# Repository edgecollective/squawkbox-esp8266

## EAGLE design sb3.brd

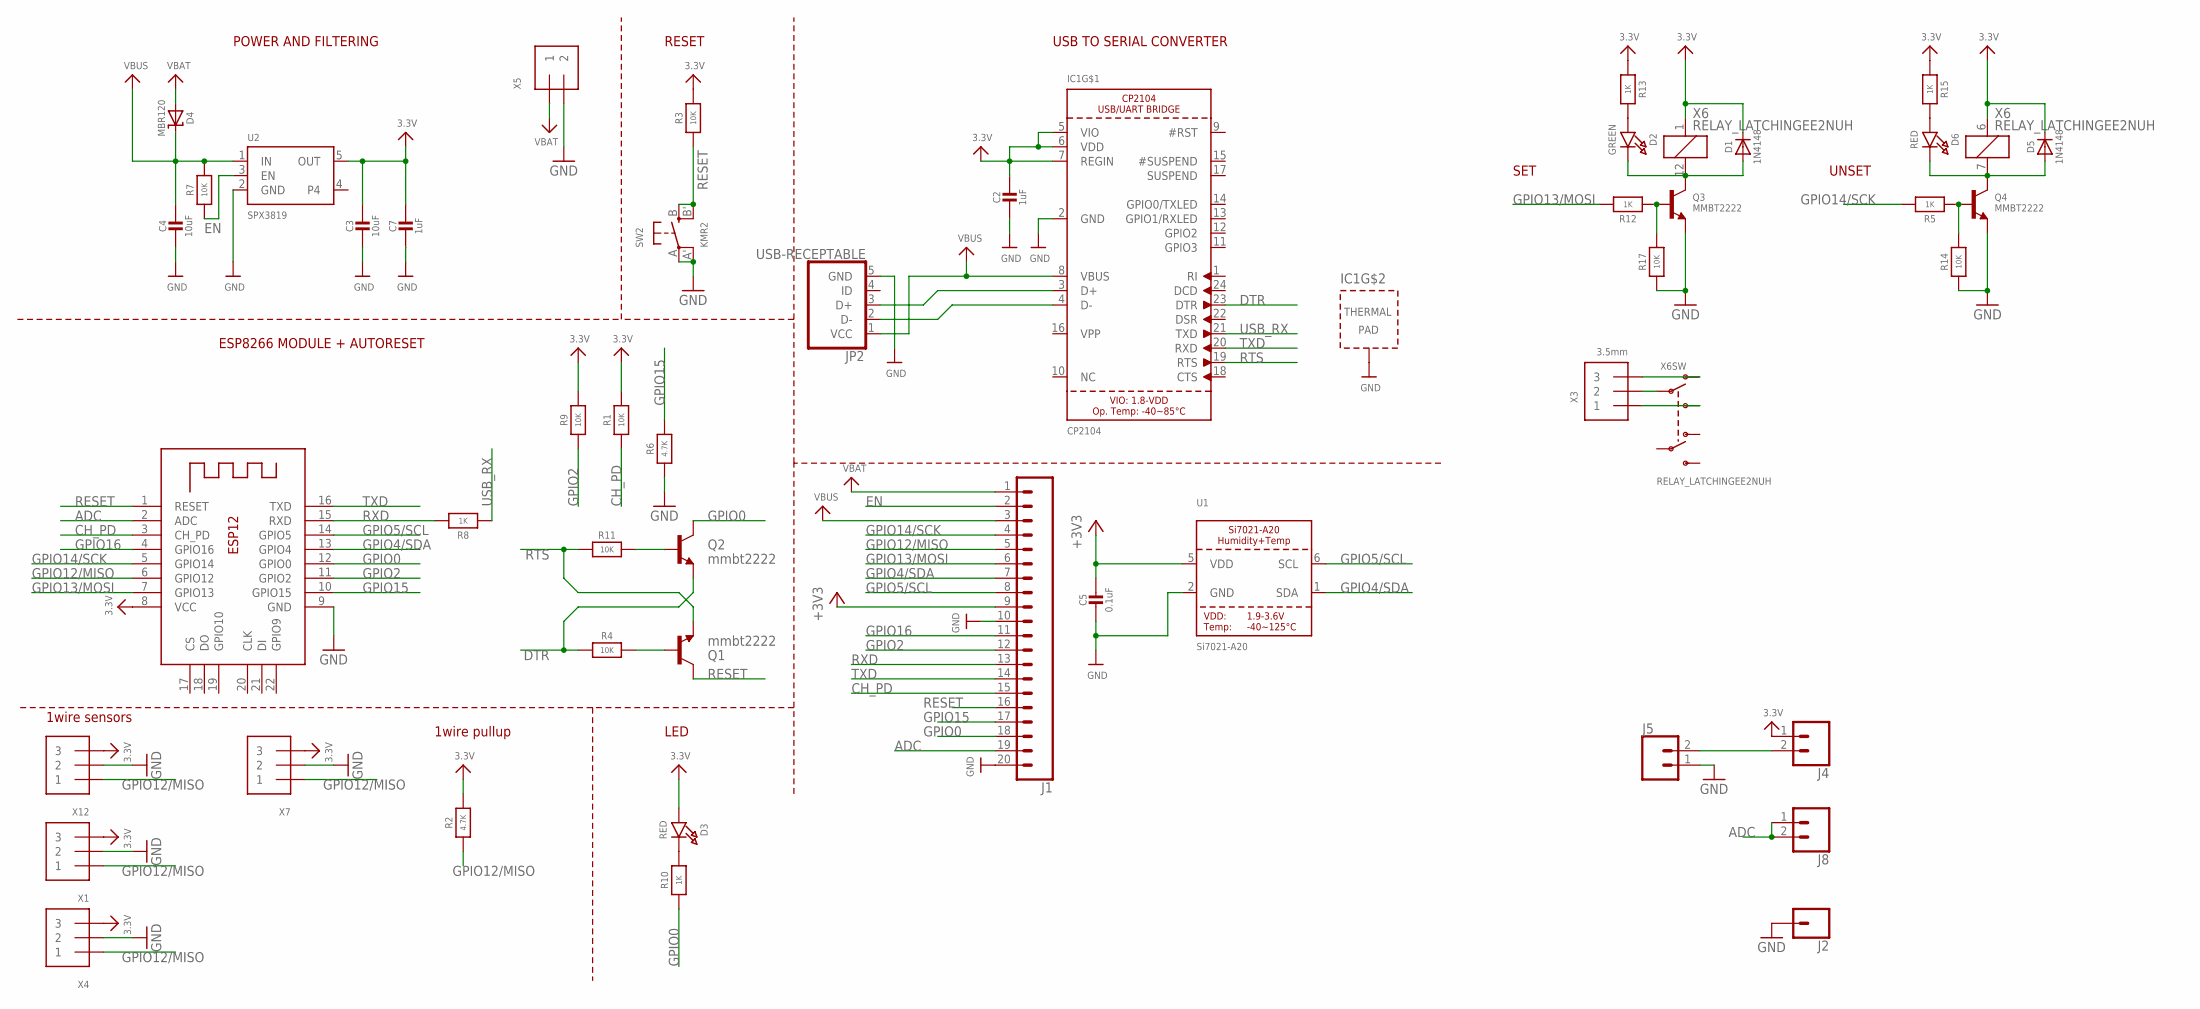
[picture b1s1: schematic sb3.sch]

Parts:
C2, C7: 1uF; 0603-NO
C3, C4: 10uF; 0603-NO
C5: 0.1uF; 0603-NO
D1, D5: 1N4148; SOD-323
D2: GREEN; CHIPLED_0805_NOOUTLINE
D3, D6: RED; CHIPLED_0805_NOOUTLINE
D4: MBR120; SOD-123
IC1: CP2104; QFN24_4MM_SMSC
J1: CONN_20; 1X20
J2: CONN_01; 1X01
J4, J8: CONN_02; 1X02
J5: CONN_023.5MM; SCREWTERMINAL-3.5MM-2
JP2: USB-RECEPTABLE; FCI-10103594-0001LF
Q1, Q2: mmbt2222; SOT23-3
Q3, Q4: MMBT2222; SOT23-R
R1, R3, R4, R7, R9, R11, R14, R17: 10K; 0603-NO
R2, R6: 4.7K; 0603-NO
R5, R8, R10, R12, R13, R15: 1K; 0603-NO
SW2: KMR2; BTN_KMR2_4.6X2.8
U1: Si7021-A20; DFN6_3X3_SI
U2: SPX3819; SOT23-5
X1, X4, X7, X12: TERMBLOCK_1X3; TERMBLOCK_1X3-3.5MM
X2: ESP-12; ESP-12E
X3: 3.5mm; TERMBLOCK_1X3-3.5MM
X5: TERMBLOCK_1X2; TERMBLOCK_1X2-3.5MM
X6: RELAY_LATCHINGEE2NUH; RELAY_EE2_LATCH

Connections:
3.3V: C2.1, C3.1, C7.1, D1.C, D3.A, D5.C, IC1.5 (VIO), IC1.6 (VDD), IC1.7 (REGIN), J4.1, R1.2, R2.2, R3.2, R9.2, R13.1, R15.1, U2.5 (OUT), X1.3, X2.8 (VCC), X4.3, X6.1, X6.6 (1), X7.3, X12.3
+3V3: C5.1, J1.9, U1.5 (VDD)
ADC: J1.19, J8.1, J8.2, X2.2 (ADC)
CH_PD: J1.15, R1.1, X2.3 (CH_PD)
COM1: X3.2, X6.9 (P1)
DTR: IC1.23 (DTR), Q2.2 (E), R4.1
EN: J1.2, R7.1, U2.3 (EN)
GND: C2.2, C3.2, C4.2, C5.2, C7.2, IC1.2 (GND), IC1.THERM (TP), J1.10, J1.20, J2.1, J5.1, JP2.5 (GND), Q3.2 (E), Q4.2 (E), R6.1, R14.1, R17.1, SW2.A, SW2.A' (P1), U1.2 (GND), U2.2 (GND), X1.2, X2.9 (GND), X4.2, X5.2, X7.2, X12.2
GPIO0: J1.18, Q2.3 (C), R10.1, X2.12 (GPIO0)
GPIO2: J1.12, R9.1, X2.11 (GPIO2)
GPIO4/SDA: J1.7, U1.1 (SDA), X2.13 (GPIO4)
GPIO5/SCL: J1.8, U1.6 (SCL), X2.14 (GPIO5)
GPIO12/MISO: J1.5, R2.1, X1.1, X2.6 (GPIO12), X4.1, X7.1, X12.1
GPIO13/MOSI: J1.6, R12.2, X2.7 (GPIO13)
GPIO14/SCK: J1.4, R5.2, X2.5 (GPIO14)
GPIO15: J1.17, R6.2, X2.10 (GPIO15)
GPIO16: J1.11, X2.4 (GPIO16)
unnamed: D1.A, D2.C, Q3.3 (C), X6.12 (2)
unnamed: IC1.3 (D+), JP2.3 (D+)
unnamed: J4.2, J5.2
unnamed: D2.A, R13.2
unnamed: D3.C, R10.2
unnamed: IC1.4 (D-), JP2.2 (D-)
unnamed: D6.A, R15.2
unnamed: Q1.1 (B), R4.2
unnamed: Q2.1 (B), R11.2
unnamed: Q3.1 (B), R12.1, R17.2
unnamed: D5.A, D6.C, Q4.3 (C), X6.7 (2)
unnamed: Q4.1 (B), R5.1, R14.2
unnamed: X3.3, X6.10 (O1)
NO1: X3.1, X6.8 (S1)
RESET: J1.16, Q1.3 (C), R3.1, SW2.B (S), SW2.B' (S1), X2.1 (RESET)
RTS: IC1.19 (RTS), Q1.2 (E), R11.1
RXD: J1.13, R8.2, X2.15 (RXD)
TXD: IC1.20 (RXD), J1.14, X2.16 (TXD)
USB_RX: IC1.21 (TXD), R8.1
VBAT: D4.A, J1.1, X5.1
VBUS: C4.1, D4.C, IC1.8 (VBUS), J1.3, JP2.1 (VCC), R7.2, U2.1 (IN)

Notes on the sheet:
POWER AND FILTERING
RESET
USB TO SERIAL CONVERTER
LED
ESP8266 MODULE + AUTORESET
1wire pullup
1wire sensors
SET
UNSET

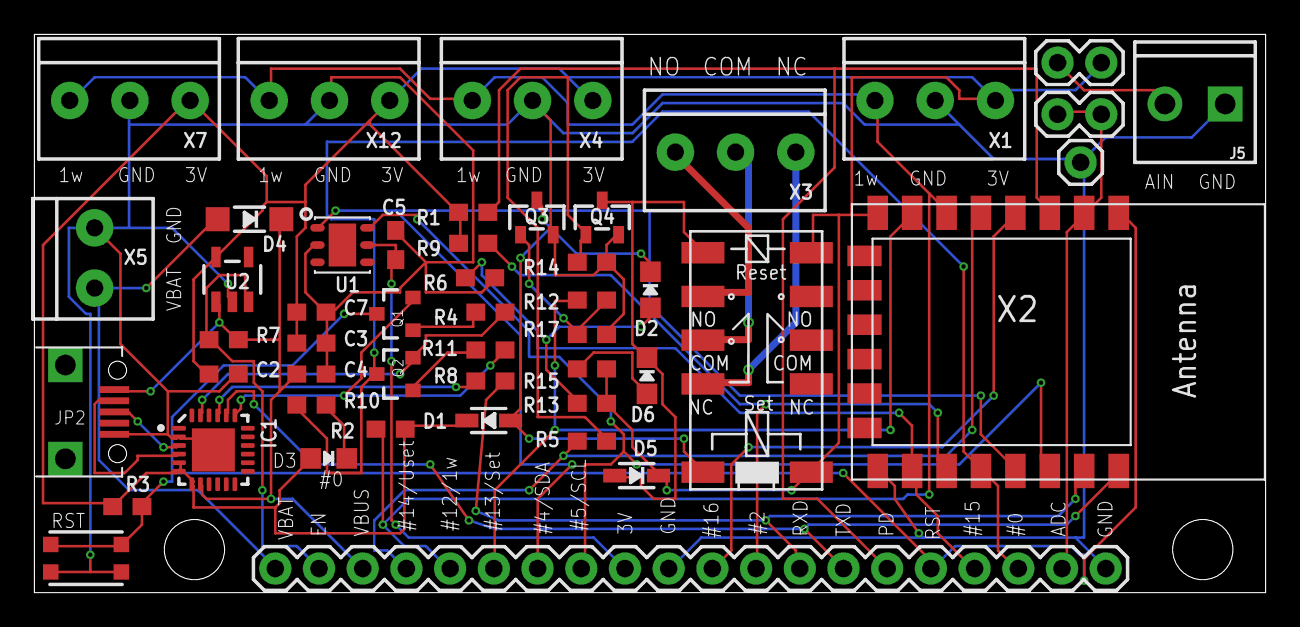
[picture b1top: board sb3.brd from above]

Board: 2 copper layers, 71.5 x 32.4 mm, 49 parts (0 on the bottom side), 38 nets.

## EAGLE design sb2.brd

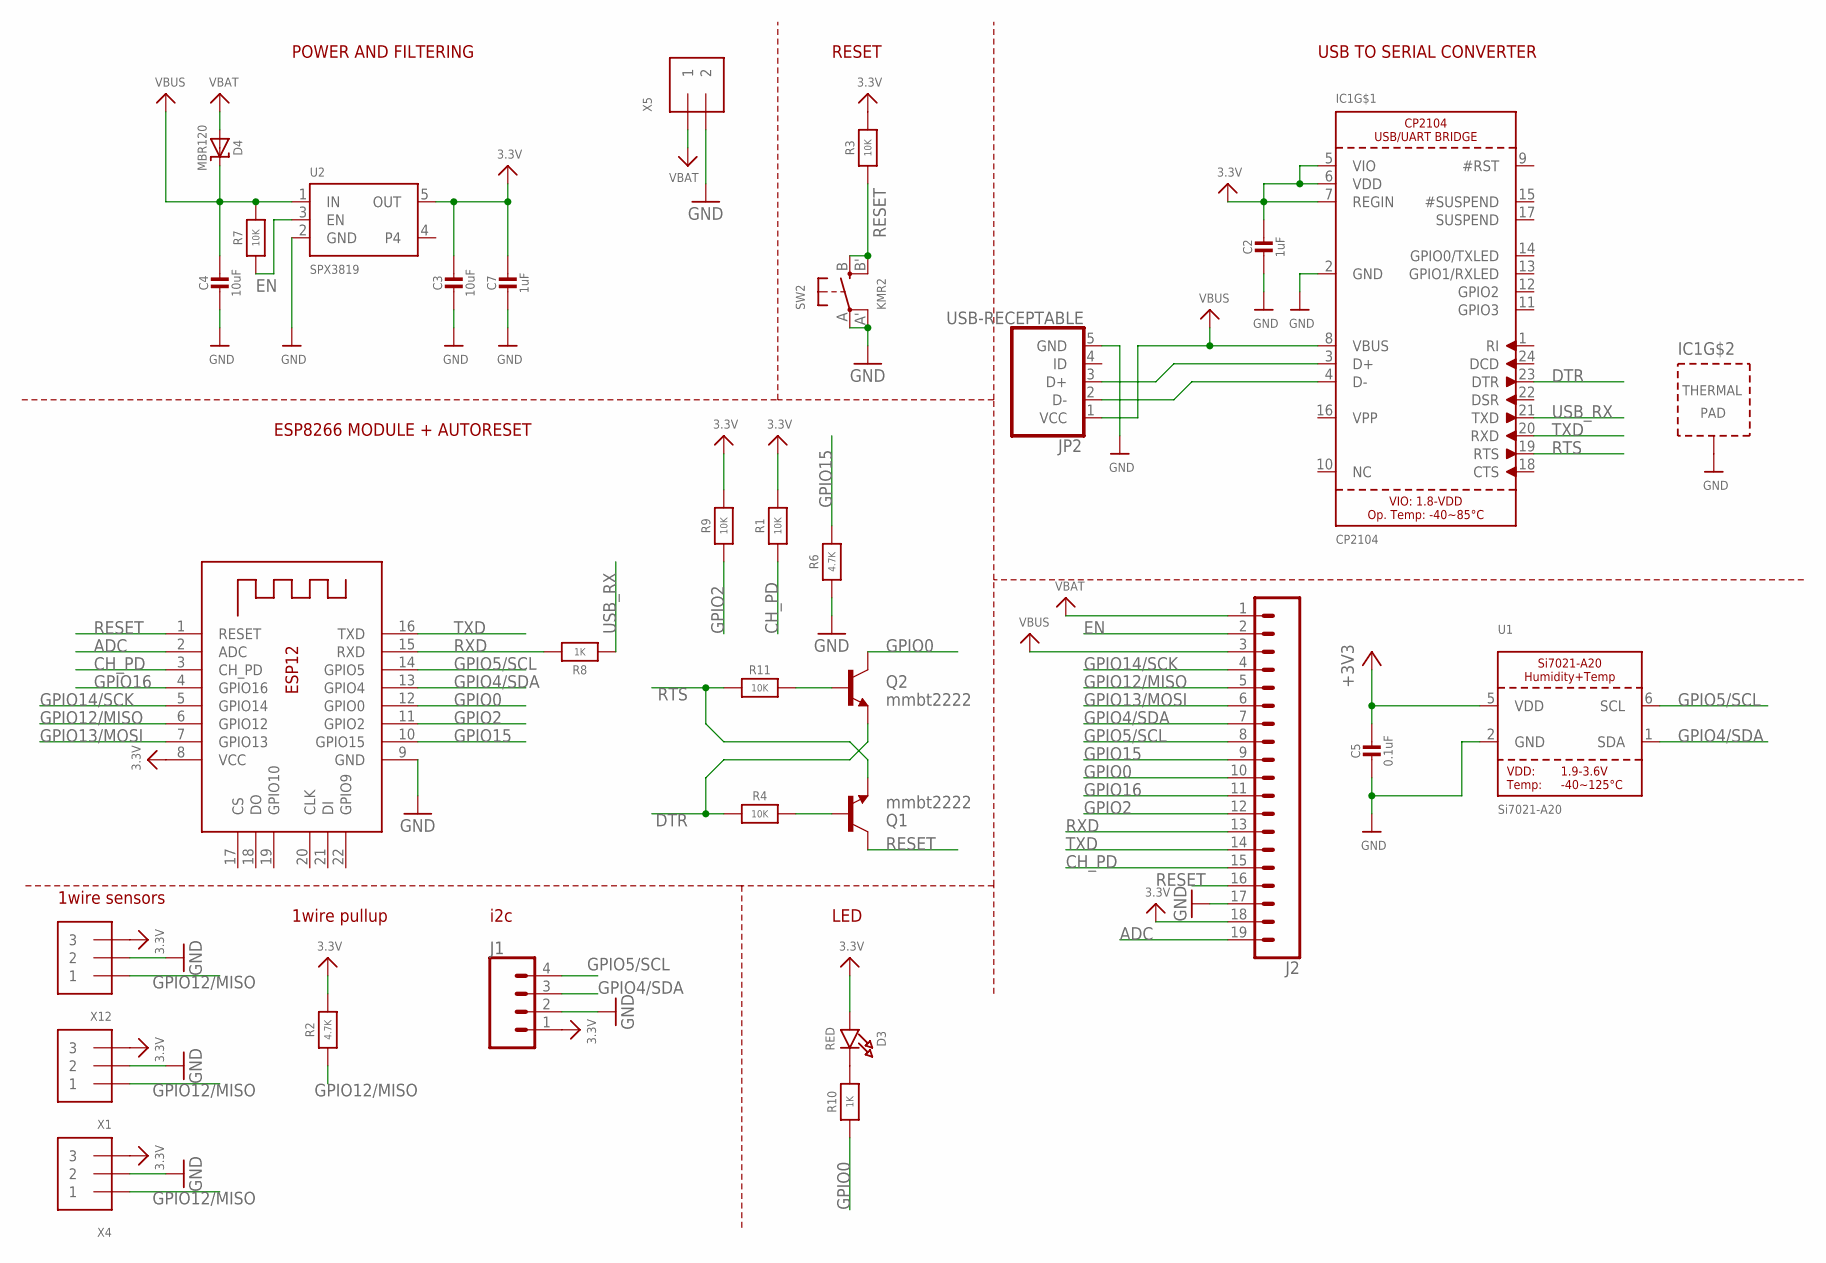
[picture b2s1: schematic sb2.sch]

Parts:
C2, C7: 1uF; 0603-NO
C3, C4: 10uF; 0603-NO
C5: 0.1uF; 0603-NO
D3: RED; CHIPLED_0805_NOOUTLINE
D4: MBR120; SOD-123
IC1: CP2104; QFN24_4MM_SMSC
J1: CONN_04SCREW; SCREWTERMINAL-3.5MM-4
J2: CONN_19; 1X19
JP2: USB-RECEPTABLE; FCI-10103594-0001LF
Q1, Q2: mmbt2222; SOT23-3
R1, R3, R4, R7, R9, R11: 10K; 0603-NO
R2, R6: 4.7K; 0603-NO
R8, R10: 1K; 0603-NO
SW2: KMR2; BTN_KMR2_4.6X2.8
U1: Si7021-A20; DFN6_3X3_SI
U2: SPX3819; SOT23-5
X1, X4, X12: TERMBLOCK_1X3; TERMBLOCK_1X3-3.5MM
X2: ESP-12; ESP-12E
X5: TERMBLOCK_1X2; TERMBLOCK_1X2-3.5MM

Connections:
3.3V: C2.1, C3.1, C7.1, D3.A, IC1.5 (VIO), IC1.6 (VDD), IC1.7 (REGIN), J1.1, J2.18, R1.2, R2.2, R3.2, R9.2, U2.5 (OUT), X1.3, X2.8 (VCC), X4.3, X12.3
+3V3: C5.1, U1.5 (VDD)
ADC: J2.19, X2.2 (ADC)
CH_PD: J2.15, R1.1, X2.3 (CH_PD)
DTR: IC1.23 (DTR), Q2.2 (E), R4.1
EN: J2.2, R7.1, U2.3 (EN)
GND: C2.2, C3.2, C4.2, C5.2, C7.2, IC1.2 (GND), IC1.THERM (TP), J1.2, J2.17, JP2.5 (GND), R6.1, SW2.A, SW2.A' (P1), U1.2 (GND), U2.2 (GND), X1.2, X2.9 (GND), X4.2, X5.2, X12.2
GPIO0: J2.10, Q2.3 (C), R10.1, X2.12 (GPIO0)
GPIO2: J2.12, R9.1, X2.11 (GPIO2)
GPIO4/SDA: J1.3, J2.7, U1.1 (SDA), X2.13 (GPIO4)
GPIO5/SCL: J1.4, J2.8, U1.6 (SCL), X2.14 (GPIO5)
GPIO12/MISO: J2.5, R2.1, X1.1, X2.6 (GPIO12), X4.1, X12.1
GPIO13/MOSI: J2.6, X2.7 (GPIO13)
GPIO14/SCK: J2.4, X2.5 (GPIO14)
GPIO15: J2.9, R6.2, X2.10 (GPIO15)
GPIO16: J2.11, X2.4 (GPIO16)
unnamed: IC1.3 (D+), JP2.3 (D+)
unnamed: D3.C, R10.2
unnamed: IC1.4 (D-), JP2.2 (D-)
unnamed: Q1.1 (B), R4.2
unnamed: Q2.1 (B), R11.2
RESET: J2.16, Q1.3 (C), R3.1, SW2.B (S), SW2.B' (S1), X2.1 (RESET)
RTS: IC1.19 (RTS), Q1.2 (E), R11.1
RXD: J2.13, R8.2, X2.15 (RXD)
TXD: IC1.20 (RXD), J2.14, X2.16 (TXD)
USB_RX: IC1.21 (TXD), R8.1
VBAT: D4.A, J2.1, X5.1
VBUS: C4.1, D4.C, IC1.8 (VBUS), J2.3, JP2.1 (VCC), R7.2, U2.1 (IN)

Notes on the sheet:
POWER AND FILTERING
RESET
USB TO SERIAL CONVERTER
LED
ESP8266 MODULE + AUTORESET
1wire pullup
1wire sensors
i2c

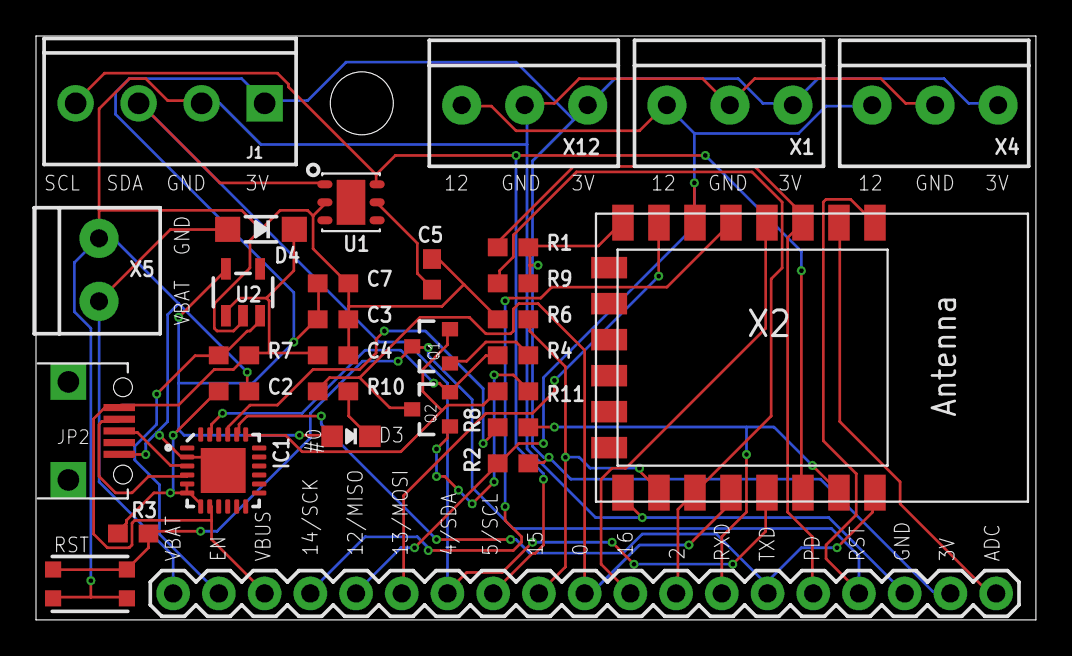
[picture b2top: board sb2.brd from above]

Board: 2 copper layers, 55.5 x 32.4 mm, 31 parts (0 on the bottom side), 28 nets.

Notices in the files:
parts and their libraries:
microbuilder: This work is placed in the public domain, and may be freely used for commercial and non-commercial work with the following conditions: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
SparkFun: Licensing: CC v3.0 Share-Alike You are welcome to use this library for commercial purposes.
